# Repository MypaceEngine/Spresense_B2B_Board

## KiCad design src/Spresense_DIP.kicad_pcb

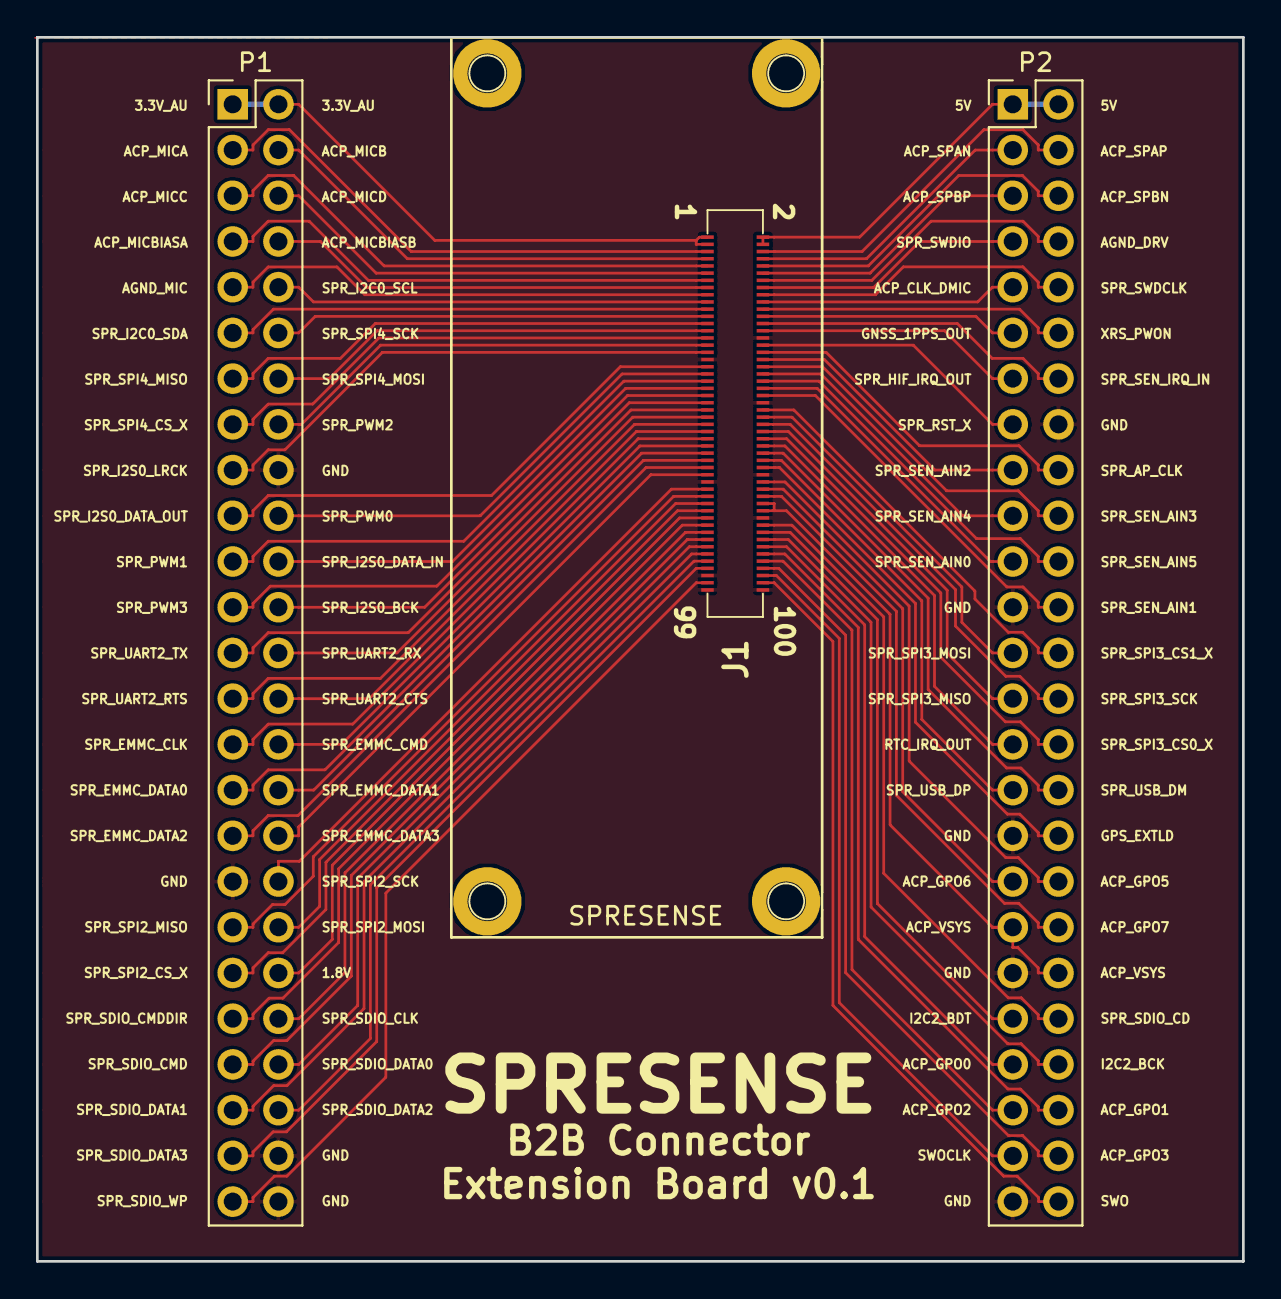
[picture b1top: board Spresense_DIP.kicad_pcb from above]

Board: 2 copper layers, 67.0 x 68.0 mm, 7 parts (0 on the bottom side), 89 nets.

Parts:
J1: DF40HC(3.0)-100DS-0.4V(58); spresense
P1, P2: CONN_02X25; Pin_Header_Straight_2x25_Pitch2.54mm
REF1**, REF2**, REF3**, REF4**: MountingHole_2.2mm_M2_DIN965_Pad

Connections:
/1.8V: J1.79, P1.40
/3.3V_AU: J1.1, J1.3, P1.1, P1.2
/5V: J1.2, J1.4, P2.1, P2.2
/ACP_CLK_DMIC: J1.20, P2.9
/ACP_GPO0: J1.88, P2.43
/ACP_GPO1: J1.90, P2.46
/ACP_GPO2: J1.92, P2.45
/ACP_GPO3: J1.94, P2.48
/ACP_GPO5: J1.70, P2.36
/ACP_GPO6: J1.72, P2.35
/ACP_GPO7: J1.74, P2.38
/ACP_MICA: J1.5, P1.3
/ACP_MICB: J1.7, P1.4
/ACP_MICBIASA: J1.13, P1.7
/ACP_MICBIASB: J1.15, P1.8
/ACP_MICC: J1.9, P1.5
/ACP_MICD: J1.11, P1.6
/ACP_SPAN: J1.8, P2.3
/ACP_SPAP: J1.6, P2.4
/ACP_SPBN: J1.10, P2.6
/ACP_SPBP: J1.12, P2.5
/ACP_VSYS: J1.76, J1.78, P2.37, P2.40
/AGND_DRV: J1.14, P2.8
/AGND_MIC: J1.17, P1.9
/GND: J1.30, J1.35, J1.48, J1.68, J1.69, J1.80, J1.95, J1.99, J1.100, P1.18, P1.35, P1.48, P1.50, P2.16, P2.23, P2.33, P2.39, P2.49
/GNSS_1PPS_OUT: J1.24, P2.11
/GPS_EXTLD: J1.66, P2.34
/I2C2_BCK: J1.86, P2.44
/I2C2_BDT: J1.84, P2.41
/RTC_IRQ_OUT: J1.60, P2.29
/SPR_AP_CLK: J1.34, P2.18
/SPR_EMMC_CLK: J1.57, P1.29
/SPR_EMMC_CMD: J1.59, P1.30
/SPR_EMMC_DATA0: J1.61, P1.31
/SPR_EMMC_DATA1: J1.63, P1.32
/SPR_EMMC_DATA2: J1.65, P1.33
/SPR_EMMC_DATA3: J1.67, P1.34
/SPR_HIF_IRQ_OUT: J1.28, P2.13
/SPR_I2C0_SCL: J1.19, P1.10
/SPR_I2C0_SDA: J1.21, P1.11
/SPR_I2S0_BCK: J1.47, P1.24
/SPR_I2S0_DATA_IN: J1.43, P1.22
/SPR_I2S0_DATA_OUT: J1.37, P1.19
/SPR_I2S0_LRCK: J1.33, P1.17
/SPR_PWM0: J1.39, P1.20
/SPR_PWM1: J1.41, P1.21
/SPR_PWM2: J1.31, P1.16
/SPR_PWM3: J1.45, P1.23
/SPR_RST_X: J1.32, P2.15
/SPR_SDIO_CD: J1.82, P2.42
/SPR_SDIO_CLK: J1.83, P1.42
/SPR_SDIO_CMD: J1.85, P1.43
/SPR_SDIO_CMDDIR: J1.81, P1.41
/SPR_SDIO_DATA0: J1.87, P1.44
/SPR_SDIO_DATA1: J1.89, P1.45
/SPR_SDIO_DATA2: J1.91, P1.46
/SPR_SDIO_DATA3: J1.93, P1.47
/SPR_SDIO_WP: J1.97, P1.49
/SPR_SEN_AIN0: J1.44, P2.21
/SPR_SEN_AIN1: J1.46, P2.24
/SPR_SEN_AIN2: J1.36, P2.17
/SPR_SEN_AIN3: J1.38, P2.20
/SPR_SEN_AIN4: J1.40, P2.19
/SPR_SEN_AIN5: J1.42, P2.22
/SPR_SEN_IRQ_IN: J1.26, P2.14
/SPR_SPI2_CS_X: J1.77, P1.39
/SPR_SPI2_MISO: J1.73, P1.37
/SPR_SPI2_MOSI: J1.75, P1.38
/SPR_SPI2_SCK: J1.71, P1.36
/SPR_SPI3_CS0_X: J1.58, P2.30
/SPR_SPI3_CS1_X: J1.50, P2.26
/SPR_SPI3_MISO: J1.56, P2.27
/SPR_SPI3_MOSI: J1.52, P2.25
/SPR_SPI3_SCK: J1.54, P2.28
/SPR_SPI4_CS_X: J1.29, P1.15
/SPR_SPI4_MISO: J1.25, P1.13
/SPR_SPI4_MOSI: J1.27, P1.14
/SPR_SPI4_SCK: J1.23, P1.12
/SPR_SWDCLK: J1.18, P2.10
/SPR_SWDIO: J1.16, P2.7
/SPR_UART2_CTS: J1.55, P1.28
/SPR_UART2_RTS: J1.53, P1.27
/SPR_UART2_RX: J1.51, P1.26
/SPR_UART2_TX: J1.49, P1.25
/SPR_USB_DM: J1.62, P2.32
/SPR_USB_DP: J1.64, P2.31
/SWO: J1.98, P2.50
/SWOCLK: J1.96, P2.47
/XRS_PWON: J1.22, P2.12
